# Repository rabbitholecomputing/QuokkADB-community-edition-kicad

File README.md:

QuokkADB Community Edition
==========================

This repository contains the KiCAD 7 schematic and PCB design files for an RP2040 Raspberry Pi Pico based USB mouse and keyboard to ADB converter.

Generating fabrication files
----------------------------

The component part numbers are stored in KiCAD schematic.
Manufacturing files, including assembly BOM, can be generated using [KiKit](https://github.com/yaqwsx/KiKit).

License
-------
This design is licensed under the CERN Open Hardware Licence Version 2 - Strongly Reciprocal. 

See `CERN-OHL-S-V2-LICENSE.txt` in the same directory as this `README.md` file

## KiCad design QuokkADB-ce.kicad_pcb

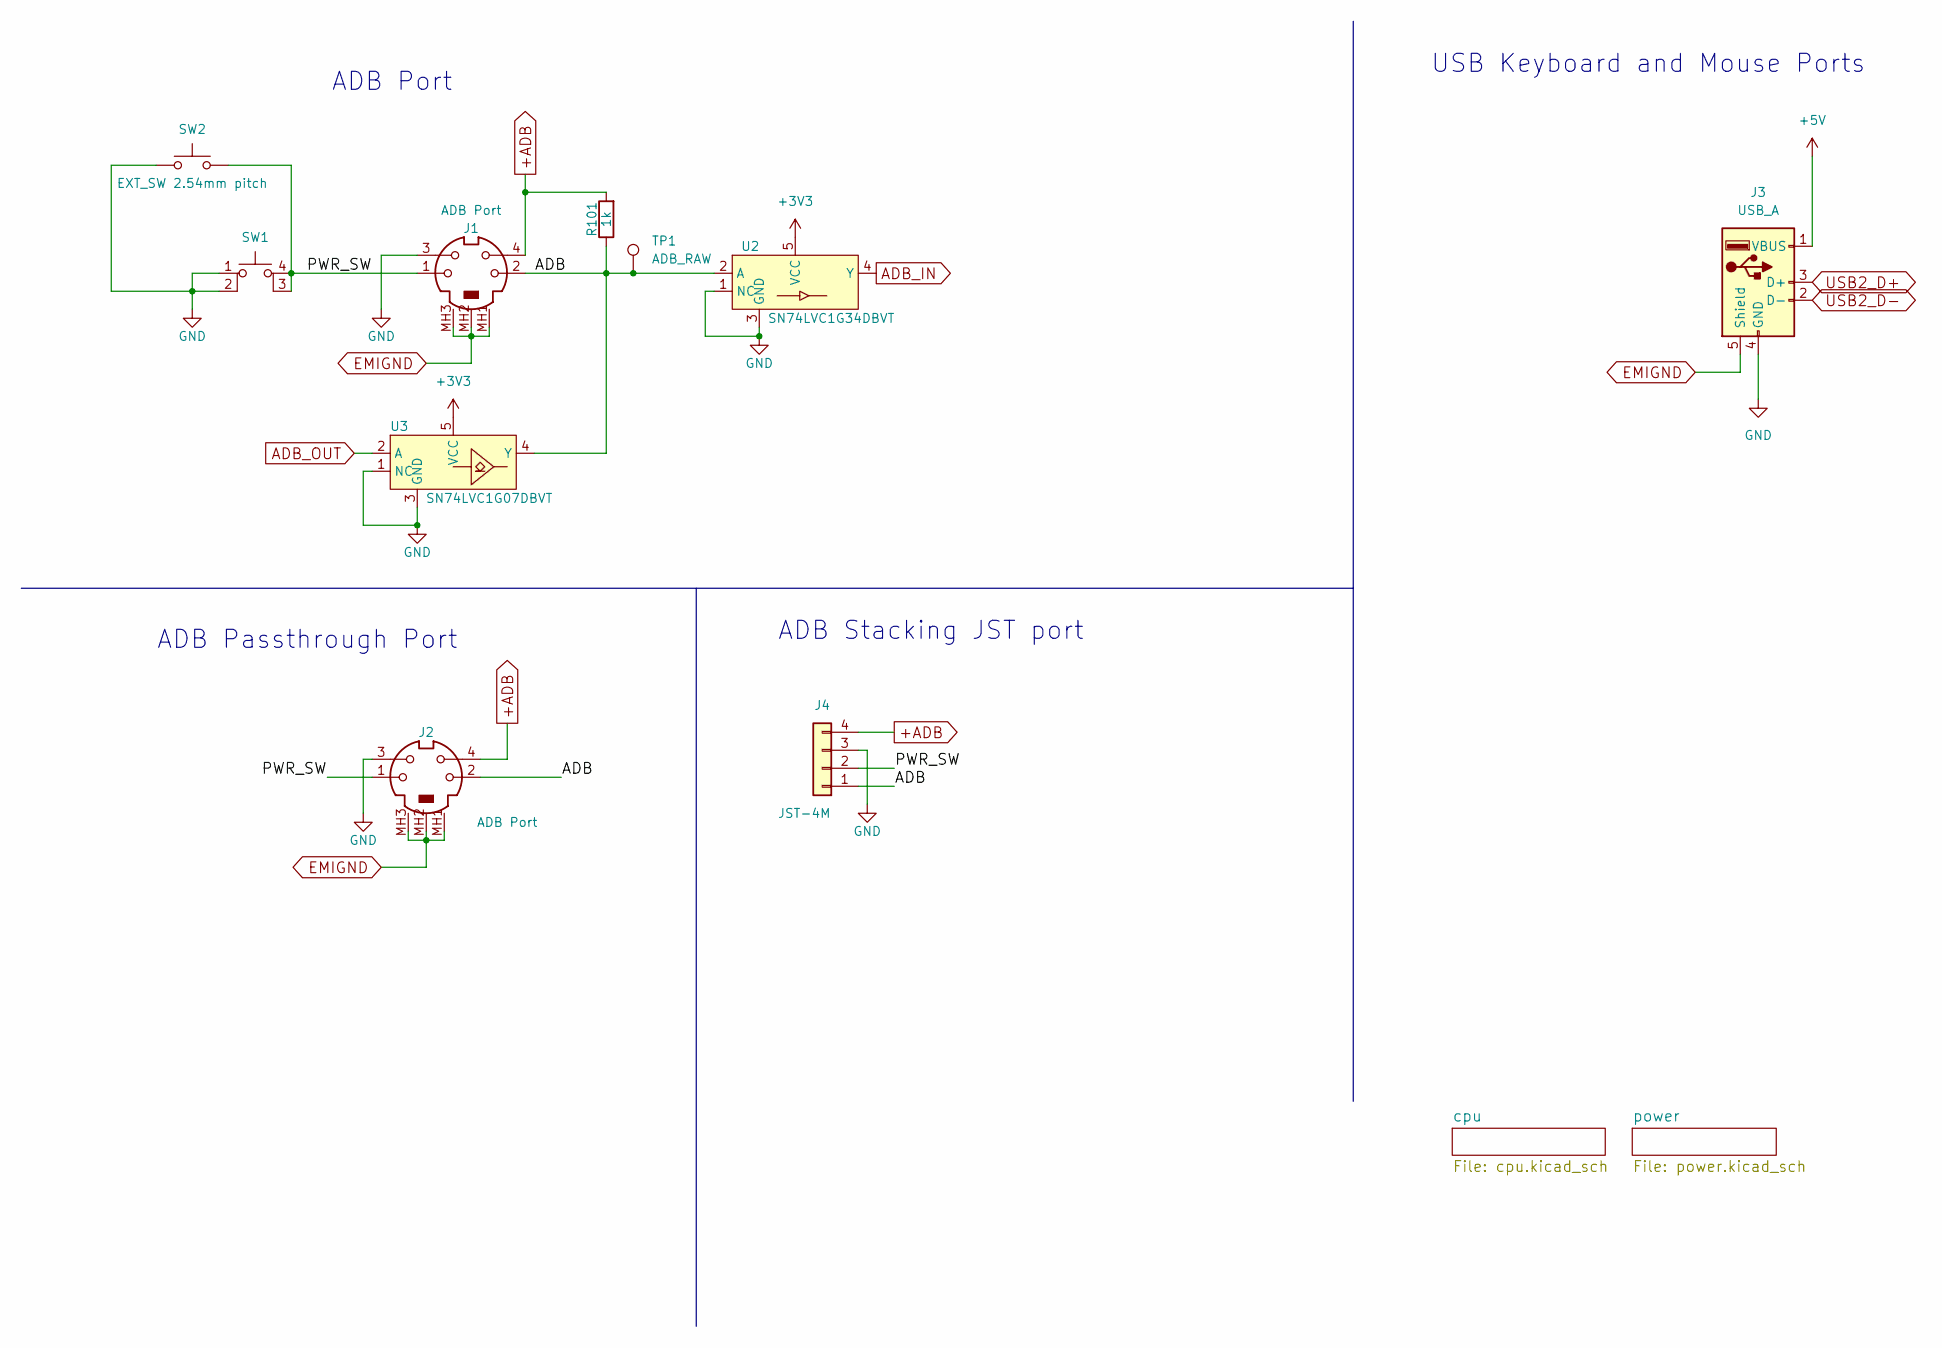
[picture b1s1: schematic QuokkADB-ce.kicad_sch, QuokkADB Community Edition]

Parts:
J1, J2: ADB Port; 57492631; PartNumber MDJ-004-FS; LCSC N/A
J3: USB_A; USB_A_Molex_67643_Horizontal; PartNumber USB-A-S-RA; LCSC N/A
J4: JST-4M; JST_SH_SM04B-SRSS-TB_1x04-1MP_P1.00mm_Horizontal
R101: 1k; R_0603_1608Metric; PartNumber RC0603FR-071KL; LCSC C21190
SW1: SW_MEC_5E; SW_SPST_TL3342F160QG; PartNumber TL3342F160QG/TR; LCSC C318884
SW2: EXT_SW 2.54mm pitch; PinHeader_1x02_P2.54mm_Vertical; LCSC N/A
TP1: ADB_RAW; Testpad_0.5mm; LCSC N/A
U2: SN74LVC1G34DBVT; SOT-23-5; PartNumber SN74LVC1G34DBVT; LCSC C840096
U3: SN74LVC1G07DBVT; SOT-23-5; PartNumber SN74LVC1G07DBVT; LCSC C7829

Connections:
+3V3: U2.5 (VCC), U3.5 (VCC); also elsewhere on the board
+5V: J3.1 (VBUS); also elsewhere on the board
+ADB: J1.4, J2.4, J4.4, R101.2; also elsewhere on the board
/ADB: J1.2, J2.2, J4.1, R101.1, TP1.1, U2.2 (A), U3.4 (Y)
/PWR_SW: J1.1, J2.1, J4.2, SW1.3 (K), SW1.4 (A), SW2.2
ADB_IN: U2.4 (Y); also elsewhere on the board
ADB_OUT: U3.2 (A); also elsewhere on the board
EMIGND: J1.MH1, J1.MH2, J1.MH3, J2.MH1, J2.MH2, J2.MH3, J3.5 (Shield); also elsewhere on the board
GND: J1.3, J2.3, J3.4 (GND), J4.3, SW1.1, SW1.2, SW2.1, U2.1 (NC), U2.3 (GND), U3.1 (NC), U3.3 (GND); also elsewhere on the board
USB2_D+: J3.3 (D+); also elsewhere on the board
USB2_D-: J3.2 (D-); also elsewhere on the board

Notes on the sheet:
ADB Passthrough Port
ADB Stacking JST port
USB Keyboard and Mouse Ports
ADB Port

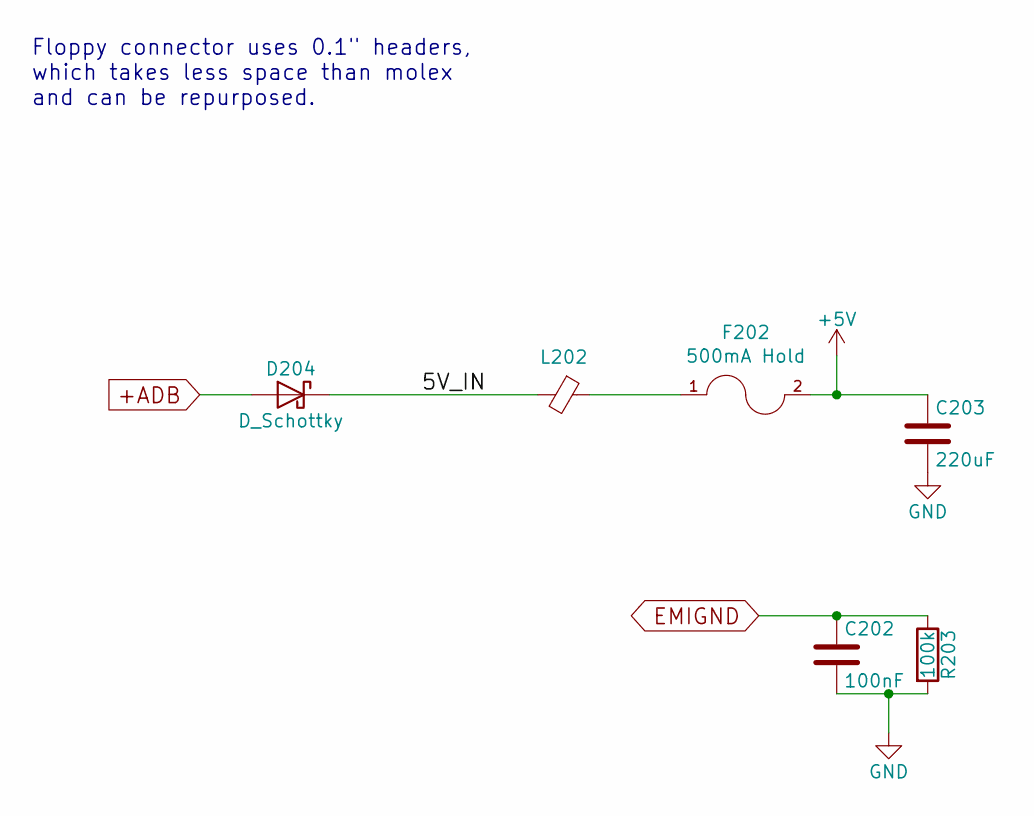
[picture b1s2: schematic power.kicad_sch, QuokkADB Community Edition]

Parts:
C202: 100nF; C_0603_1608Metric; PartNumber CL10B104KB8NNWC; LCSC C14663
C203: 220uF; CP_Elec_6.3x7.7; PartNumber UUD1C221MCL1GS; LCSC C2887273
D204: D_Schottky; D_SOD-123; PartNumber MBRX120LF-TP; LCSC C8598
F202: 500mA Hold; Fuse_1206_3216Metric; PartNumber 0ZCJ0050FF2G; LCSC C220147
L202: Ferrite_Bead_Small; L_0603_1608Metric; PartNumber PE-0603FB601ST; LCSC C1002
R203: 100k; R_0603_1608Metric; PartNumber RC0603FR-07100KL; LCSC C25803

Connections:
+5V: C203.1, F202.2; also elsewhere on the board
+ADB: D204.2 (A); also elsewhere on the board
/power/5V_IN: D204.1 (K), L202.2
EMIGND: C202.1, R203.1; also elsewhere on the board
GND: C202.2, C203.2, R203.2; also elsewhere on the board
unnamed: F202.1, L202.1

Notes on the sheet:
Floppy connector uses 0.1" headers, which takes less space than molex and can be repurposed.

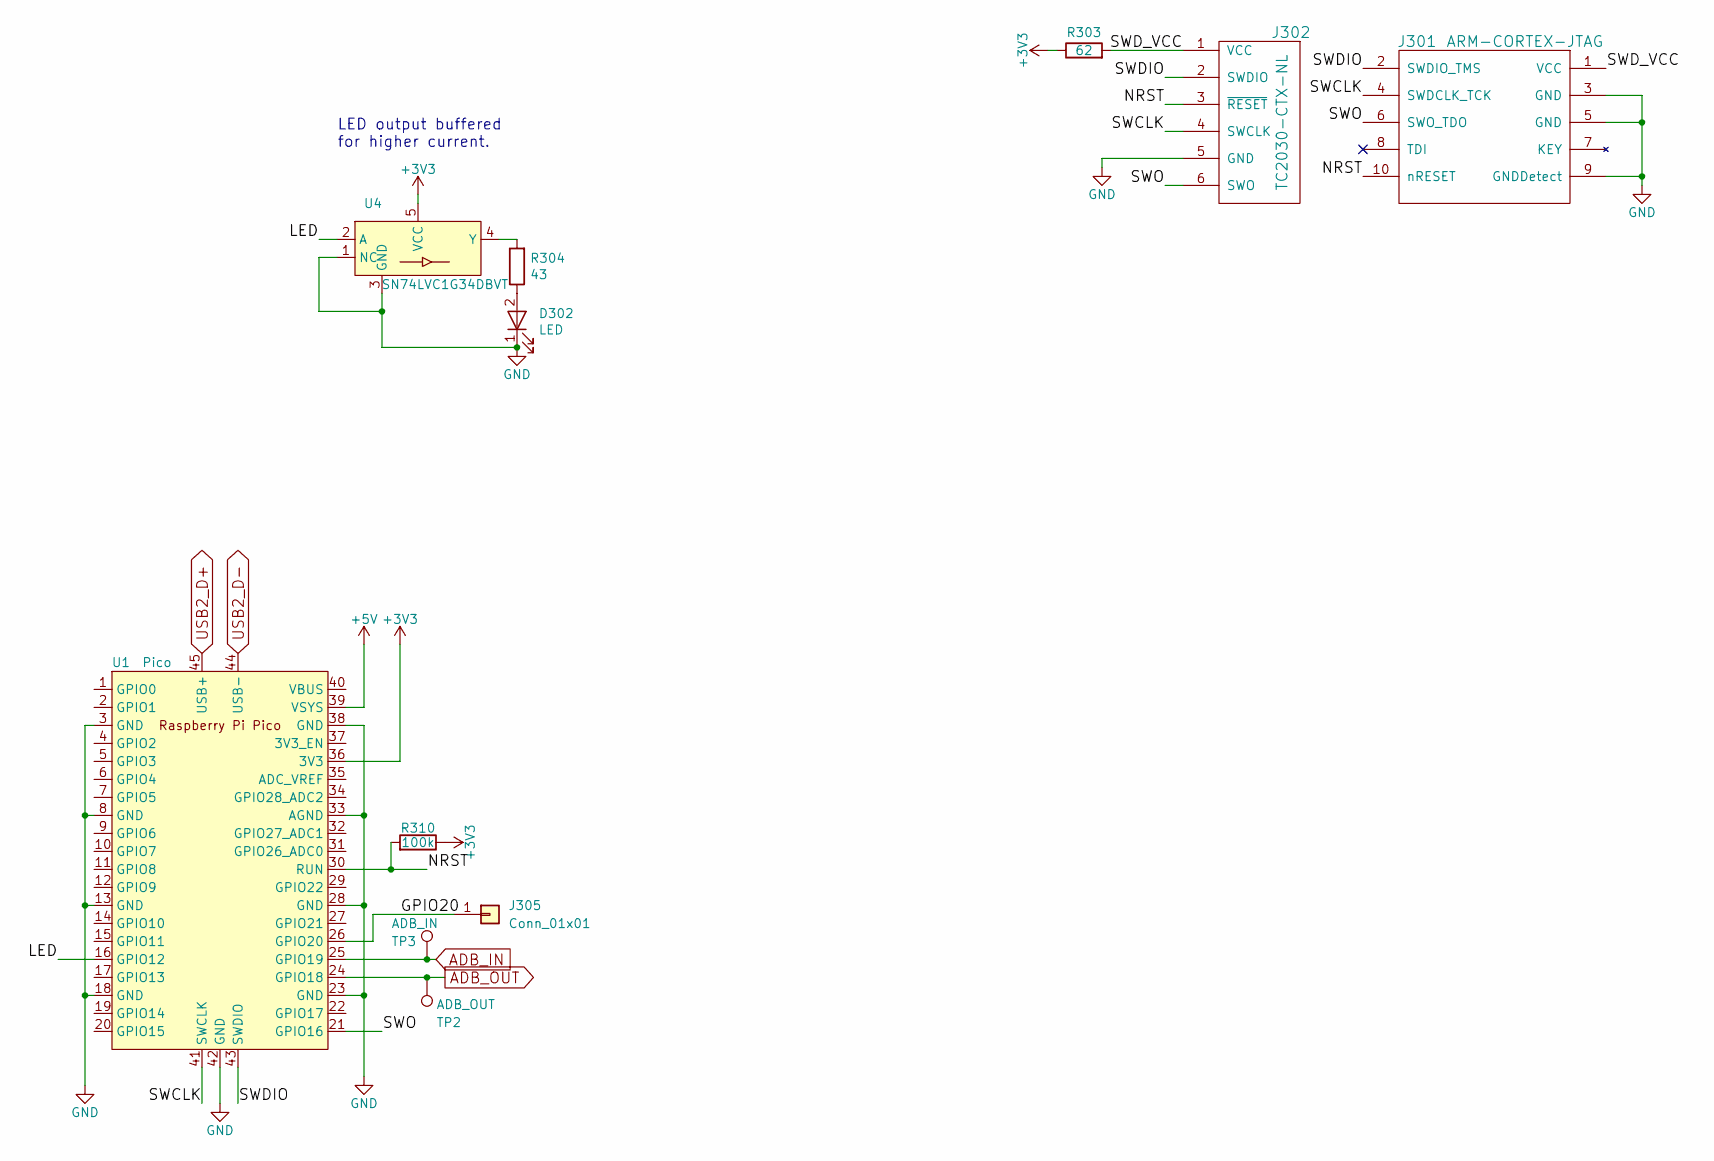
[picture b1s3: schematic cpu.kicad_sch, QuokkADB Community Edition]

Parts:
D302: LED; LED_0805_2012Metric; PartNumber LY R976-PS-36; LCSC C434435
J301: ARM-CORTEX-JTAG; PinHeader_2x05_P1.27mm_Vertical; LCSC N/A
J302: TC2030-CTX-NL; TC2030; LCSC N/A
J305: Conn_01x01; PinHeader_1x01_P2.54mm_Vertical
R303: 62; R_0603_1608Metric; PartNumber RC0603FR-0762RL; LCSC C25252
R304: 43; R_0603_1608Metric; PartNumber RC0603FR-0743RL; LCSC C227904
R310: 100k; R_0603_1608Metric; PartNumber RC0603FR-07100KL; LCSC C25803
TP2: ADB_OUT; Testpad_0.5mm; LCSC N/A
TP3: ADB_IN; Testpad_0.5mm; LCSC N/A
U1: Pico; RPi_Pico_SMD_TH
U4: SN74LVC1G34DBVT; SOT-23-5; PartNumber SN74LVC1G34DBVT; LCSC C840096

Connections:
+3V3: R303.1, R310.1, U1.36 (3V3), U4.5 (VCC); also elsewhere on the board
+5V: U1.39 (VSYS); also elsewhere on the board
/cpu/GPIO20: J305.1, U1.26 (GPIO20)
/cpu/LED: U1.16 (GPIO12), U4.2 (A)
/cpu/NRST: J301.10 (nRESET), J302.3 (~RESET), R310.2, U1.30 (RUN)
/cpu/SWCLK: J301.4 (SWDCLK_TCK), J302.4 (SWCLK), U1.41 (SWCLK)
/cpu/SWDIO: J301.2 (SWDIO_TMS), J302.2 (SWDIO), U1.43 (SWDIO)
/cpu/SWD_VCC: J301.1 (VCC), J302.1 (VCC), R303.2
/cpu/SWO: J301.6 (SWO_TDO), J302.6 (SWO), U1.21 (GPIO16)
ADB_IN: TP3.1, U1.25 (GPIO19); also elsewhere on the board
ADB_OUT: TP2.1, U1.24 (GPIO18); also elsewhere on the board
GND: D302.1 (K), J301.3 (GND), J301.5 (GND), J301.9 (GNDDetect), J302.5 (GND), U1.3 (GND), U1.8 (GND), U1.13 (GND), U1.18 (GND), U1.23 (GND), U1.28 (GND), U1.33 (AGND), U1.38 (GND), U1.42 (GND), U4.1 (NC), U4.3 (GND); also elsewhere on the board
unnamed: D302.2 (A), R304.1
unnamed: R304.2, U4.4 (Y)
USB2_D+: U1.45 (USB+); also elsewhere on the board
USB2_D-: U1.44 (USB-); also elsewhere on the board

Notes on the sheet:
LED output buffered for higher current.

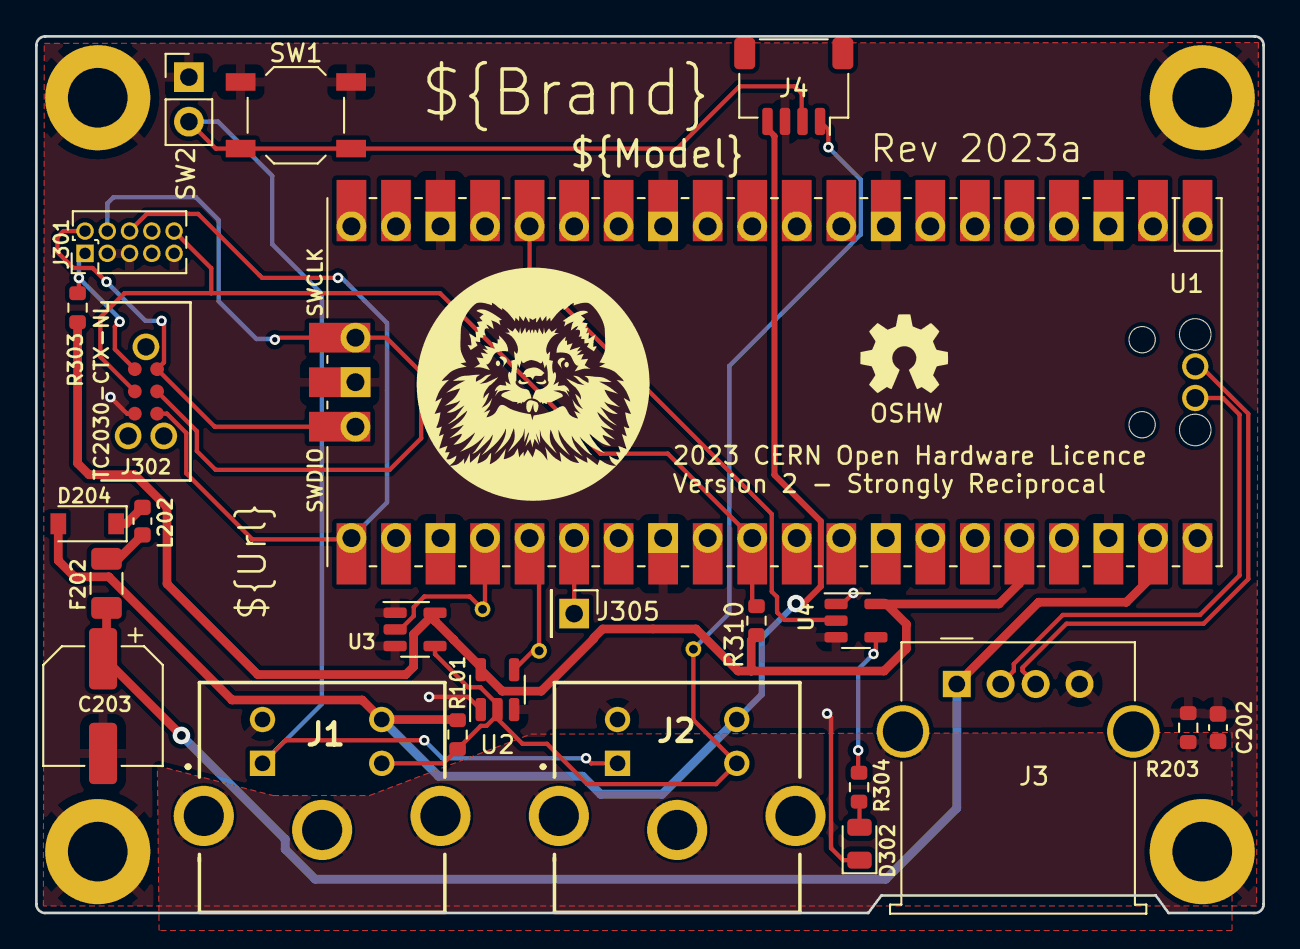
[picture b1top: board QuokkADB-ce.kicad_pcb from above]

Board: 2 copper layers, 70.0 x 50.0 mm, 27 parts (0 on the bottom side), 22 nets.

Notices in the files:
QuokkADB-ce.kicad_pcb:
2023 CERN Open Hardware Licence Version 2 - Strongly Reciprocal
